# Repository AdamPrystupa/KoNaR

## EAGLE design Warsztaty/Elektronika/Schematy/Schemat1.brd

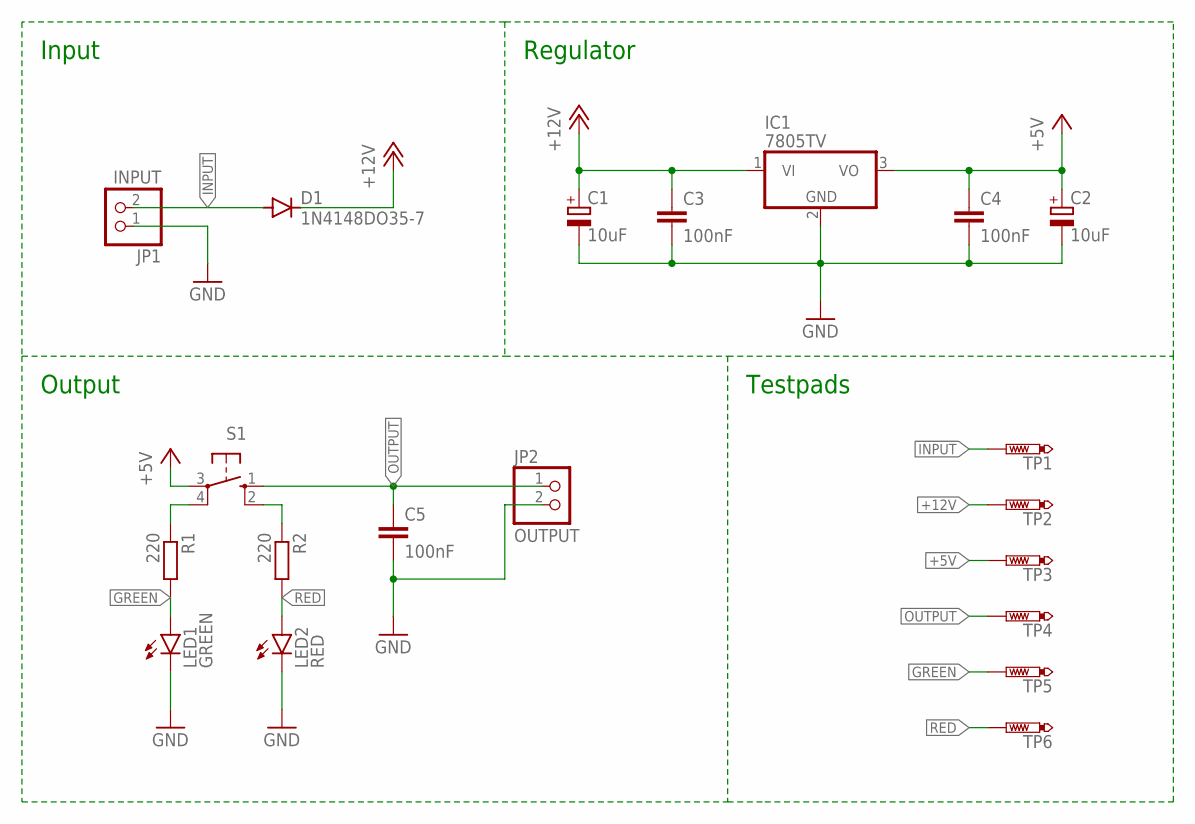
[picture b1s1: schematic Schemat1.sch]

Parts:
C1, C2: 10uF; PANASONIC_D
C3, C4, C5: 100nF; C025-025X050
D1: 1N4148DO35-7; DO35-7
IC1: 7805TV; TO220V
JP1: INPUT; 1X02
JP2: OUTPUT; 1X02
LED1: GREEN; LED5MM
LED2: RED; LED5MM
R1, R2: 220; 0207/10
S1: 10-XX; B3F-10XX
TP1, TP2, TP3, TP4, TP5, TP6: PTR1TP15R; TP15R

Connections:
+5V: C2.+, C4.1, IC1.3 (VO), S1.3, TP3.TP
+12V: C1.+, C3.1, D1.C, IC1.1 (VI), TP2.TP
GND: C1.-, C2.-, C3.2, C4.2, C5.2, IC1.2 (GND), JP1.1, JP2.2, LED1.K (C), LED2.K (C)
GREEN: LED1.A, R1.2, TP5.TP
INPUT: D1.A, JP1.2, TP1.TP
unnamed: R1.1, S1.4 (P1)
unnamed: R2.1, S1.2 (S1)
OUTPUT: C5.1, JP2.1, S1.1 (S), TP4.TP
RED: LED2.A, R2.2, TP6.TP

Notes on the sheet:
Input
Regulator
Output
Testpads

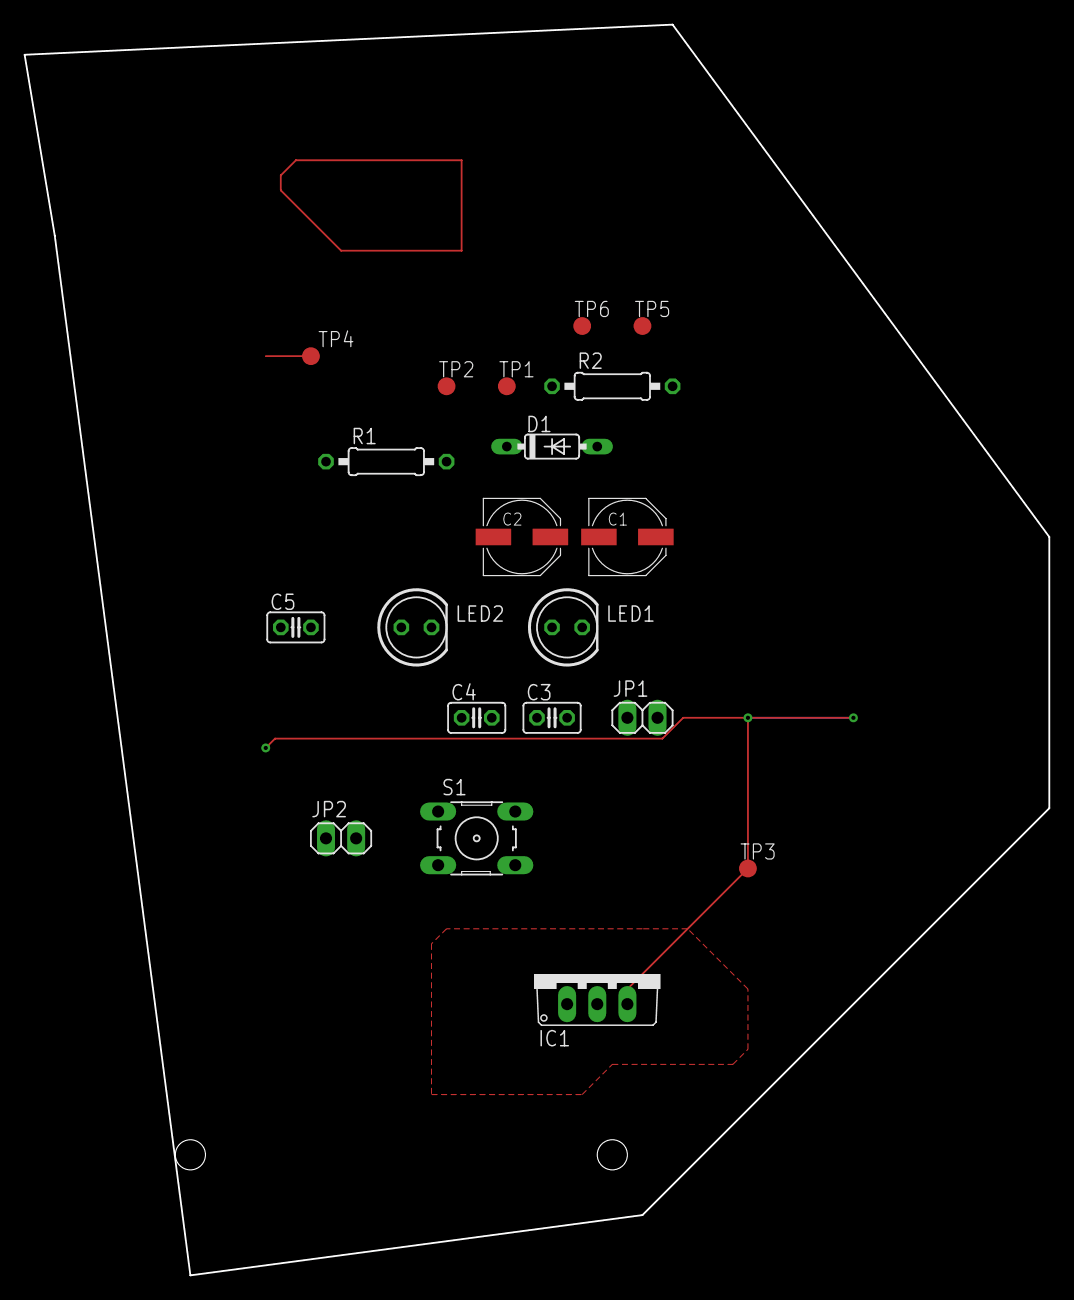
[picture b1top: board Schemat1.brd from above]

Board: 2 copper layers, 86.4 x 105.4 mm, 20 parts (0 on the bottom side), 9 nets.

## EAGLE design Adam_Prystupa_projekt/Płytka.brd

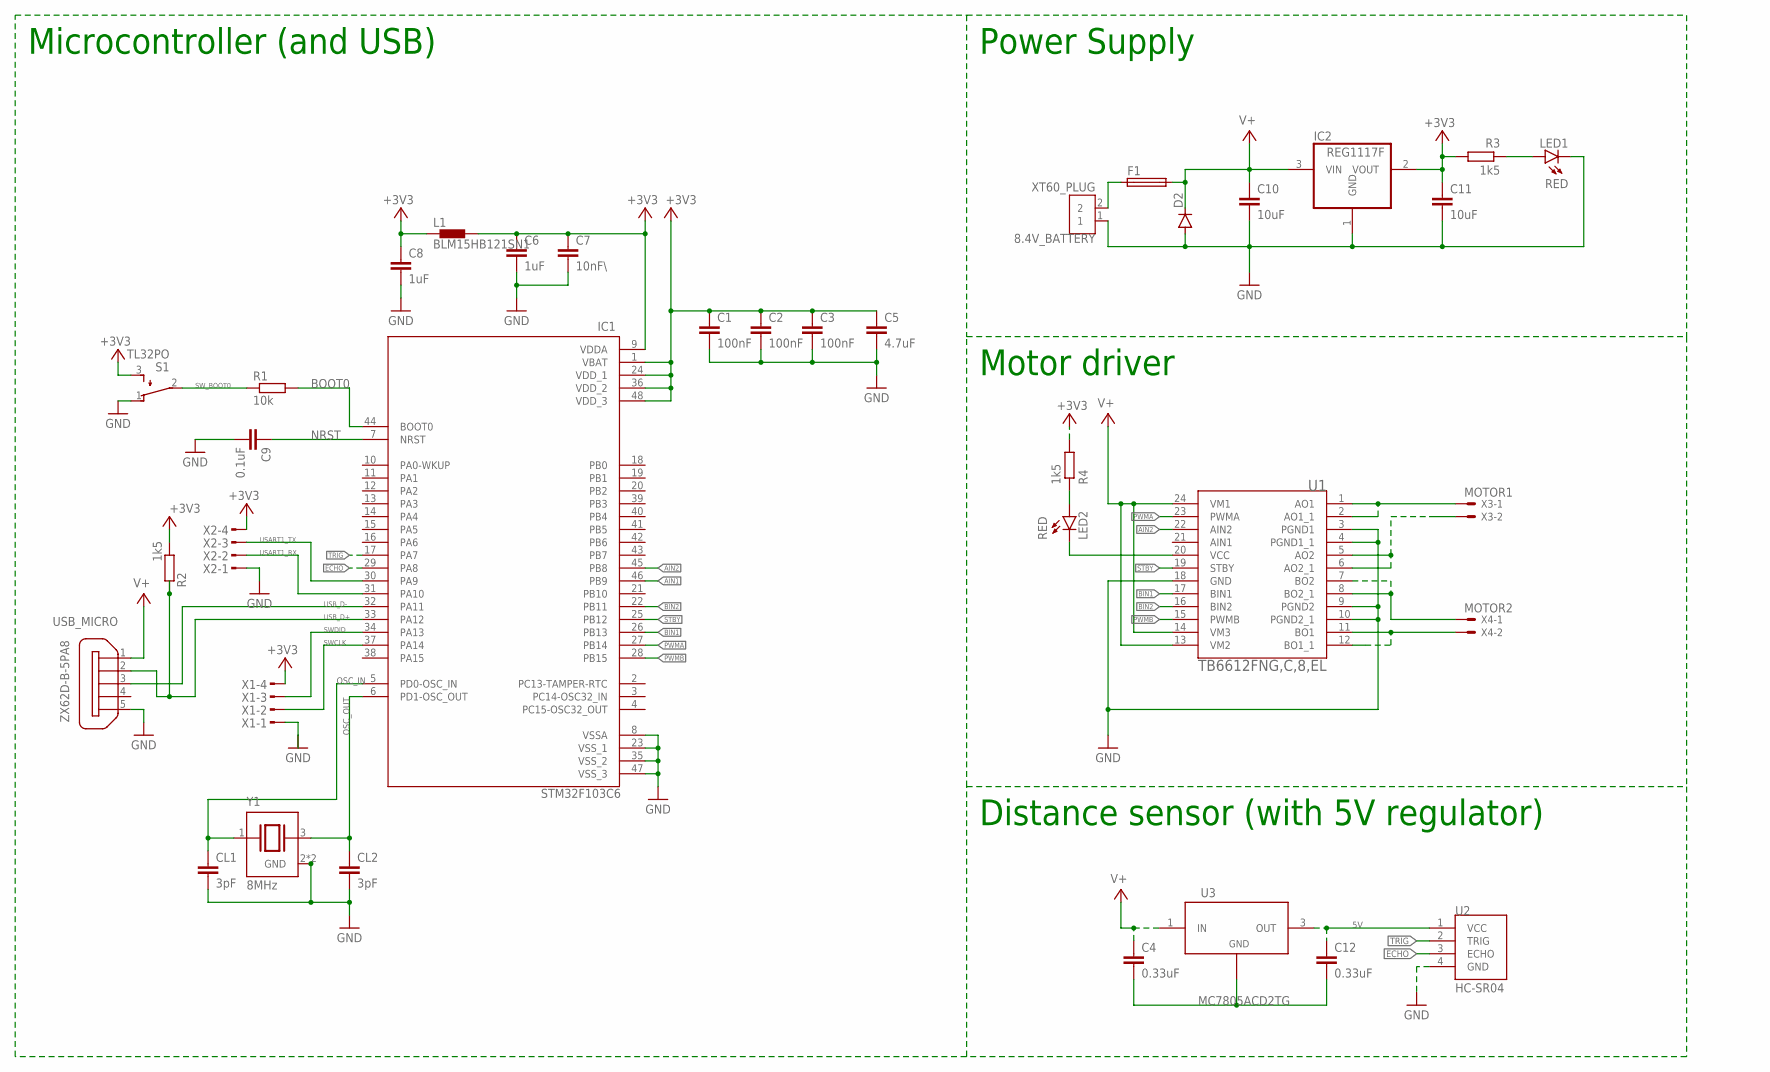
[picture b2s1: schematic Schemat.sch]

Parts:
8.4V_BATTERY: XT60_PLUG; AMASS_XT60PB-M
C1, C2, C3: 100nF; C0805
C4, C12: 0.33uF; C0805
C5: 4.7uF; C0805
C6, C8: 1uF; C0805
C7: 10nF\; C0805
C9: 0.1uF; C0805
C10, C11: 10uF; C0805
CL1, CL2: 3pF; C0805
D2: 1N4004; DO41-10
F1: 19559
IC1: STM32F103C6; QFP50P900X900X160-48N
IC2: REG1117F; DD-3
L1: BLM15HB121SN1; 0402
LED1, LED2: RED; LED3MM
R1: 10k; 0204V
R2: 1k5; 0204V
R3, R4: 1k5; R0805
S1: TL32PO; TL3XPO
U1: TB6612FNG,C,8,EL; SSOP-24
U2: HC-SR04; XCVR_HC-SR04
U3: MC7805ACD2TG; D2PAK
USB_MICRO: ZX62D-B-5PA8
X1, X2: MTOP-4
X3: MOTOR1; 53048-02
X4: MOTOR2; 53048-02
Y1: 8MHz; XTAL_ABMM2-8.0000MHZ-E1-T

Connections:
5V: C12.1, U2.1 (VCC), U3.3 (OUT)
8.4V: 8.4V_BATTERY.2, F1.1
+3V3: C1.1, C2.1, C3.1, C5.1, C6.1, C7.1, C8.1, C11.1, IC1.1 (VBAT), IC1.9 (VDDA), IC1.24 (VDD_1), IC1.36 (VDD_2), IC1.48 (VDD_3), IC2.2 (VOUT), L1.1, L1.2, R2.2, R3.2, R4.2, S1.3 (S), X1.4, X2.4
AIN1: IC1.46 (PB9)
AIN2: IC1.45 (PB8)
AO1: U1.1 (AO1), U1.2 (AO1_1), X3.1
AO2: U1.5 (AO2), U1.6 (AO2_1), X3.2
BIN1: IC1.26 (PB13), U1.17 (BIN1)
BIN2: IC1.22 (PB11)
BO1: U1.11 (BO1), U1.12 (BO1_1), X4.2
BO2: U1.7 (BO2), U1.8 (BO2_1), X4.1
BOOT0: IC1.44 (BOOT0), R1.2
ECHO: IC1.29 (PA8), U2.3 (ECHO)
GND: 8.4V_BATTERY.1, C1.2, C2.2, C3.2, C5.2, C6.2, C7.2, C8.2, C9.2, C10.2, C11.2, CL1.1, CL2.1, D2.A, IC1.8 (VSSA), IC1.23 (VSS_1), IC1.35 (VSS_2), IC1.47 (VSS_3), IC2.1 (GND), LED1.K (C), S1.1 (O), U1.3 (PGND1), U1.4 (PGND1_1), U1.9 (PGND2), U1.10 (PGND2_1), U1.18 (GND), U2.4 (GND), USB_MICRO.5, X1.1, X2.1, Y1.2 (GND), Y1.4 (GND)
GND1: C4.2, C12.2, U3.2 (ADJ/GND)
unnamed: LED1.A, R3.1
unnamed: LED2.A, R4.1
NRST: C9.1, IC1.7 (NRST)
OSC_IN: CL1.2, IC1.5 (PD0-OSC_IN), Y1.1
OSC_OUT: CL2.2, IC1.6 (PD1-OSC_OUT), Y1.3 (2)
PWMA: IC1.27 (PB14)
PWMB: IC1.28 (PB15)
STBY: IC1.25 (PB12), U1.19 (STBY)
SWCLK: IC1.37 (PA14), X1.2
SWDID: IC1.34 (PA13), X1.3
SW_BOOT0: R1.1, S1.2
TRIG: IC1.17 (PA7), U2.2 (TRIG)
USART1_RX: IC1.31 (PA10), X2.2
USART1_TX: IC1.30 (PA9), X2.3
USB_D+: IC1.33 (PA12), R2.1, USB_MICRO.2
USB_D-: IC1.32 (PA11), USB_MICRO.3
V+: C4.1, C10.1, D2.C, F1.2, IC2.3 (VIN), U1.13 (VM2), U1.14 (VM3), U1.24 (VM1), U3.1 (IN), USB_MICRO.1
VCC: LED2.K (C), U1.20 (VCC)

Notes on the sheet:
Power Supply
Microcontroller (and USB)
Motor driver
Distance sensor (with 5V regulator)

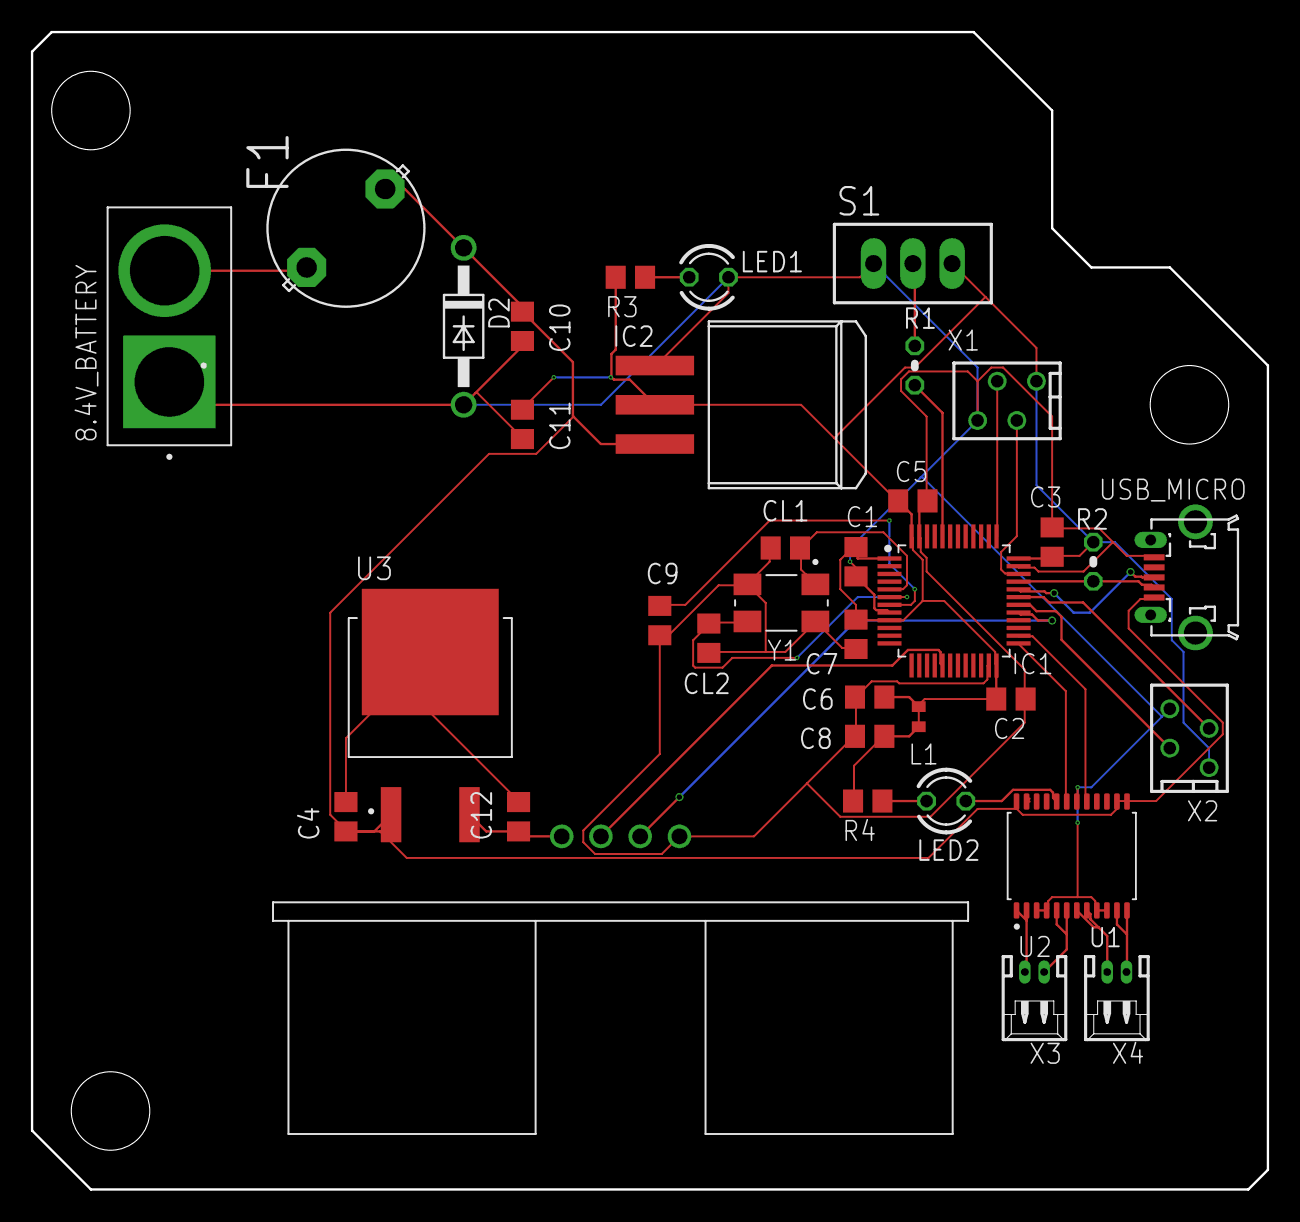
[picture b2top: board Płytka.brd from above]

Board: 2 copper layers, 80.0 x 74.9 mm, 36 parts (0 on the bottom side), 28 nets.

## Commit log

2024-05-03 uzupełnienie repo
2024-05-03 naprawa segregator
2024-05-04 laczenie hierarchiczne schematu
2024-05-04 wstepnie skonczony schemat
2024-05-05 wstepnie gotowy schemat
2024-05-05 chyba gotowy schemat
2024-05-12 stan przed usunięciem jednego czujnika lini
2024-05-25 Wstępny wyglad robota i płytki
2024-05-27 koncowy projekt plytki i chyba model tez
2024-05-30 prawdopodobnie koncowa wersja płytki
2024-05-30 ostateczna wersja mechaniczna
2024-05-30 ostateczna wersja plytki
2024-05-30 dodane modele 3d elektroniki
2024-05-31 wersja ostateczna plytki - gotowe gerbery do zamowienia
2024-05-31 wersja ostateczna plytki - gotowe gerbery do zamowienia
2024-06-03 ostatnie poprawki
2024-06-04 ostateczna wersja płytki
